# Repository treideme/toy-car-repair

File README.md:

# Mercedes Toy Repair

This repo contains schematics, drawings, and firmware of the controller
for my sons broken Mercedes.

See [my blogpost](https://reidemeister.com/blog/2022.07.04) for more information.

---- 
Pull requests are welcome. For major changes, please open an issue first to discuss what you would like to change.

## License
[MIT](LICENSE.md)

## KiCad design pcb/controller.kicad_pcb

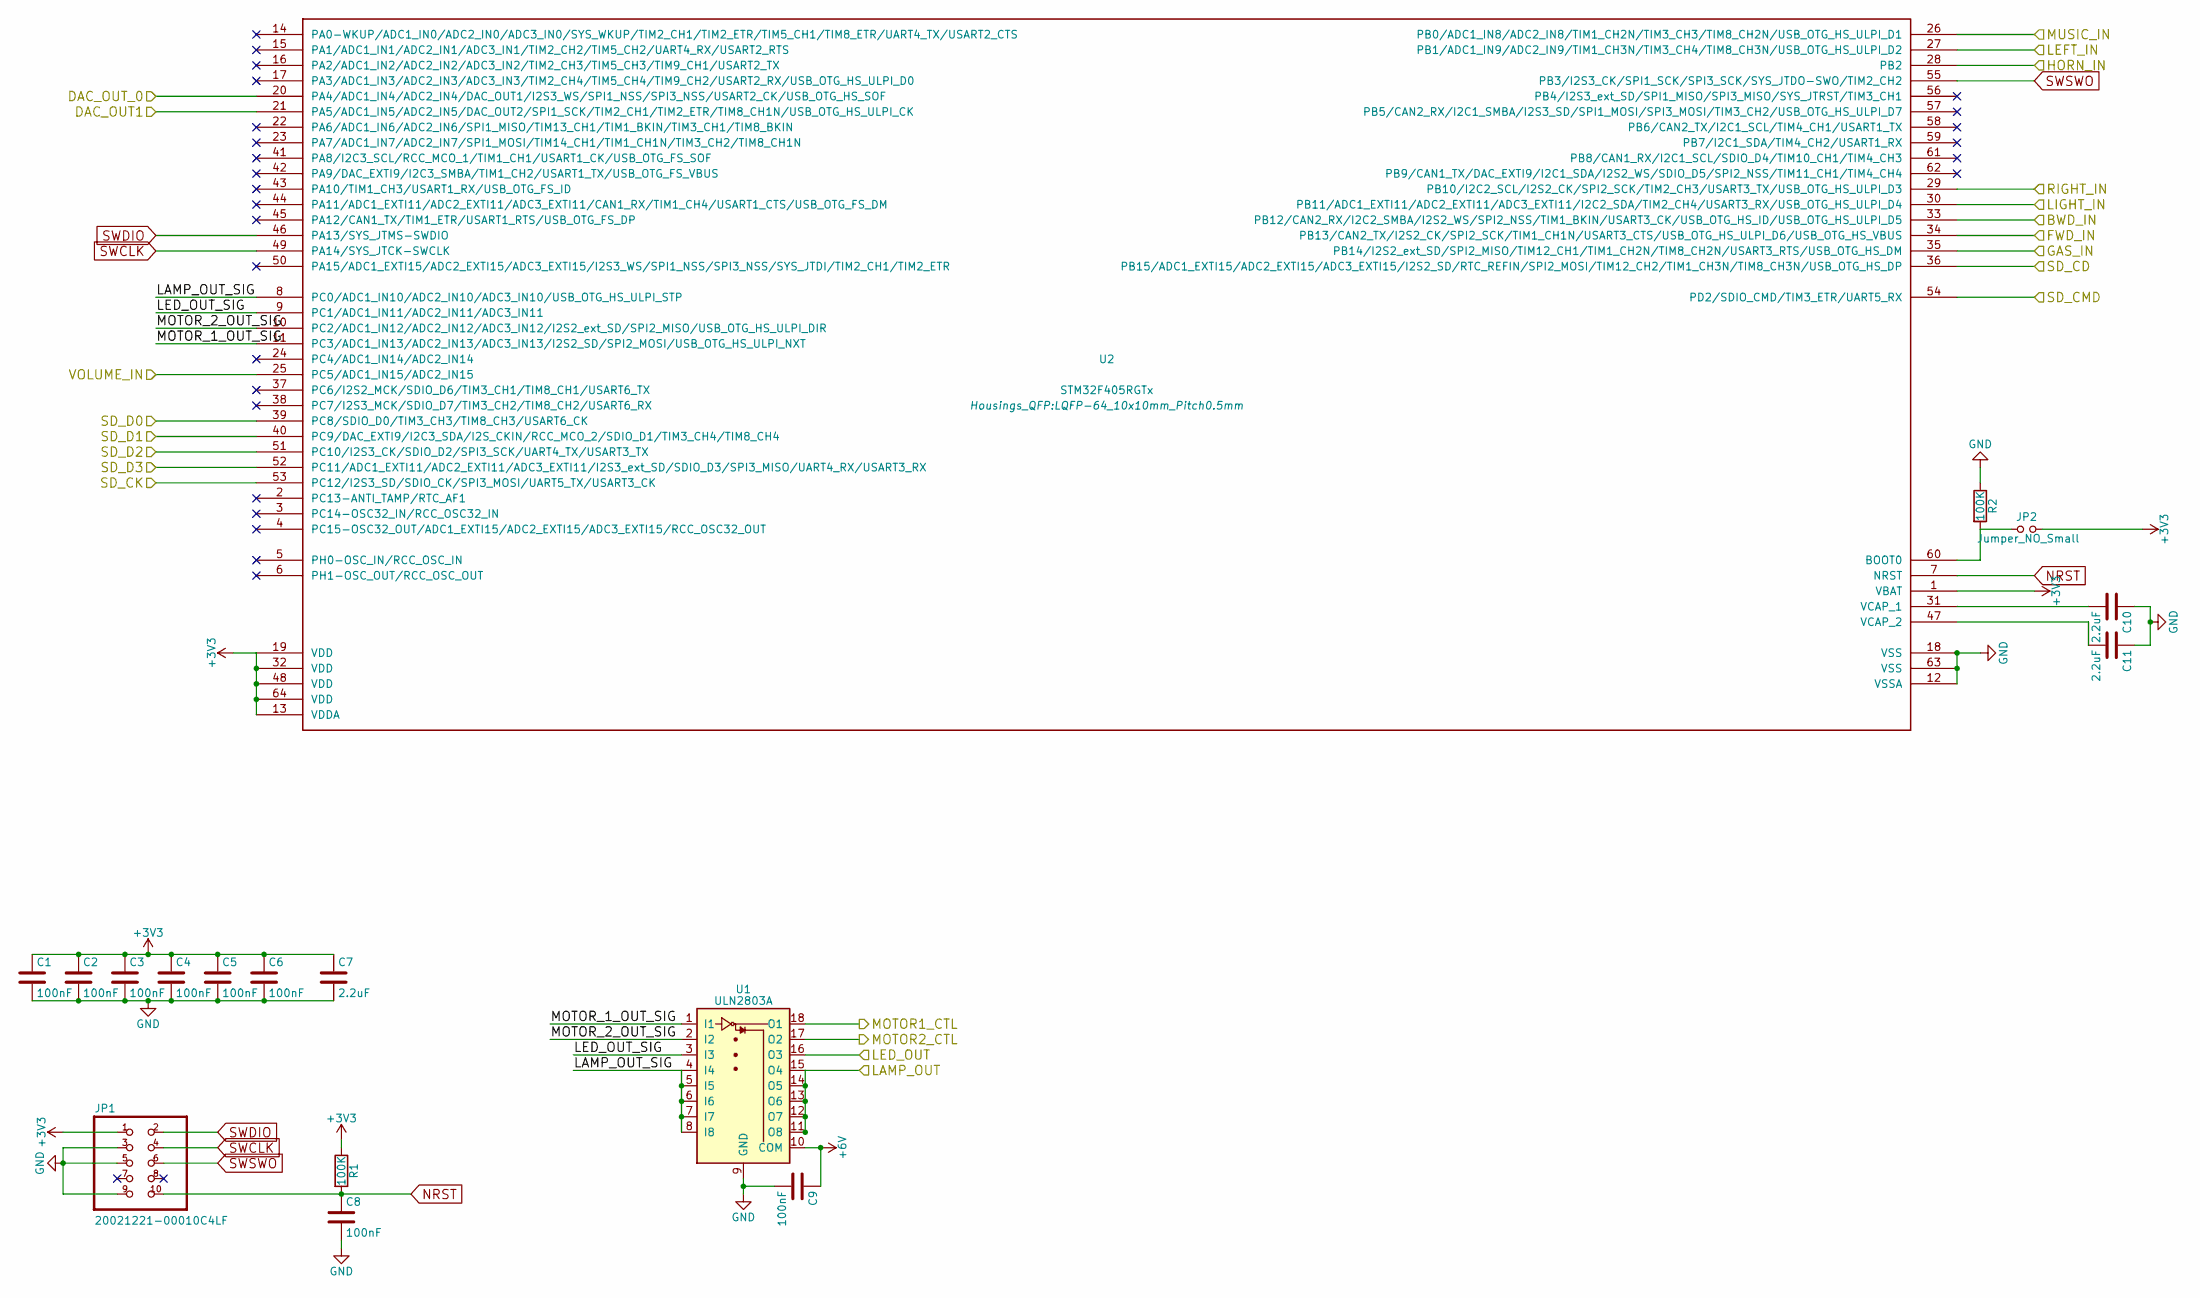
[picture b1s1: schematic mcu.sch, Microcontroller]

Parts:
C1, C2, C3, C4, C5, C6, C8, C9: 100nF; C_0603_HandSoldering; MFRPN GCM188R71C104KA37D; LCSC C184760
C7, C10, C11: 2.2uF; C_0603_HandSoldering; MFRPN GRM188B31A225KE33D; LCSC C85991
JP1: 20021221-00010C4LF
JP2: Jumper_NO_Small; SolderJumper-2_P1.3mm_Open_Pad1.0x1.5mm
R1, R2: 100K; R_0603_HandSoldering; MFRPN ERJUP3J104V; LCSC C491207
U1: ULN2803A; SOIC-18W_7.5x11.6mm_Pitch1.27mm; MFRPN ULN2803ADWR; LCSC C9683
U2: STM32F405RGTx; LQFP-64_10x10mm_Pitch0.5mm; MFRPN STM32F405RGT6; LCSC C15742

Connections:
+3V3: C1.1, C2.1, C3.1, C4.1, C5.1, C6.1, C7.1, JP1.1, JP2.2, R1.1, U2.1 (VBAT), U2.13 (VDDA), U2.19 (VDD), U2.32 (VDD), U2.48 (VDD), U2.64 (VDD); also elsewhere on the board
+6V: C9.1, U1.10 (COM); also elsewhere on the board
/External/BACKWARD_IN: U2.33 (PB12/CAN2_RX/I2C2_SMBA/I2S2_WS/SPI2_NSS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); also elsewhere on the board
/External/FORWARD_IN: U2.34 (PB13/CAN2_TX/I2S2_CK/SPI2_SCK/TIM1_CH1N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); also elsewhere on the board
/External/GAS_IN: U2.35 (PB14/I2S2_ext_SD/SPI2_MISO/TIM12_CH1/TI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); also elsewhere on the board
/External/HORN_IN: U2.28 (PB2); also elsewhere on the board
/External/LED_OUT: U1.16 (O3); also elsewhere on the board
/External/LEFT_IN: U2.27 (PB1/ADC1_IN9/ADC2_IN9/TIM1_CH3N/TIM3_CH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); also elsewhere on the board
/External/LIGHT_IN: U2.30 (PB11/ADC1_EXTI11/ADC2_EXTI11/ADC3_EXTI1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); also elsewhere on the board
/External/MUSIC_IN: U2.26 (PB0/ADC1_IN8/ADC2_IN8/TIM1_CH2N/TIM3_CH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); also elsewhere on the board
/External/RIGHT_IN: U2.29 (PB10/I2C2_SCL/I2S2_CK/SPI2_SCK/TIM2_CH3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); also elsewhere on the board
/External/SD_CMD: U2.54 (PD2/SDIO_CMD/TIM3_ETR/UART5_RX); also elsewhere on the board
/External/SD_D0: U2.39 (PC8/SDIO_D0/TIM3_CH3/TIM8_CH3/USART6_CK); also elsewhere on the board
/External/SD_D1: U2.40 (PC9/DAC_EXTI9/I2C3_SDA/I2S_CKIN/RCC_MCO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); also elsewhere on the board
/External/SD_D2: U2.51 (PC10/I2S3_CK/SDIO_D2/SPI3_SCK/UART4_TX/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); also elsewhere on the board
/External/SD_D3: U2.52 (PC11/ADC1_EXTI11/ADC2_EXTI11/ADC3_EXTI1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); also elsewhere on the board
/External/VOLUME_IN: U2.25 (PC5/ADC1_IN15/ADC2_IN15); also elsewhere on the board
/Microcontroller/DAC_OUT1: U2.21 (PA5/ADC1_IN5/ADC2_IN5/DAC_OUT2/SPI1_SCK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); also elsewhere on the board
/Microcontroller/DAC_OUT_0: U2.20 (PA4/ADC1_IN4/ADC2_IN4/DAC_OUT1/I2S3_WS/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); also elsewhere on the board
/Microcontroller/LAMP_OUT: U1.11 (O8), U1.12 (O7), U1.13 (O6), U1.14 (O5), U1.15 (O4); also elsewhere on the board
/Microcontroller/LAMP_OUT_SIG: U1.4 (I4), U1.5 (I5), U1.6 (I6), U1.7 (I7), U1.8 (I8), U2.8 (PC0/ADC1_IN10/ADC2_IN10/ADC3_IN10/USB_O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)
/Microcontroller/LED_OUT_SIG: U1.3 (I3), U2.9 (PC1/ADC1_IN11/ADC2_IN11/ADC3_IN11)
/Microcontroller/MOTOR1_CTL: U1.18 (O1); also elsewhere on the board
/Microcontroller/MOTOR2_CTL: U1.17 (O2); also elsewhere on the board
/Microcontroller/MOTOR_1_OUT_SIG: U1.1 (I1), U2.11 (PC3/ADC1_IN13/ADC2_IN13/ADC3_IN13/I2S2_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)
/Microcontroller/MOTOR_2_OUT_SIG: U1.2 (I2), U2.10 (PC2/ADC1_IN12/ADC2_IN12/ADC3_IN12/I2S2_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)
/Microcontroller/SD_CD: U2.36 (PB15/ADC1_EXTI15/ADC2_EXTI15/ADC3_EXTI1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); also elsewhere on the board
/Microcontroller/SD_CK: U2.53 (PC12/I2S3_SD/SDIO_CK/SPI3_MOSI/UART5_TX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); also elsewhere on the board
GND: C1.2, C2.2, C3.2, C4.2, C5.2, C6.2, C7.2, C8.2, C9.2, C10.1, C11.1, JP1.3, JP1.5, JP1.9, R2.1, U1.9 (GND), U2.12 (VSSA), U2.18 (VSS), U2.63 (VSS); also elsewhere on the board
NRST: C8.1, JP1.10, R1.2, U2.7 (NRST)
unnamed: C10.2, U2.31 (VCAP_1)
unnamed: C11.2, U2.47 (VCAP_2)
unnamed: JP2.1, R2.2, U2.60 (BOOT0)
SWCLK: JP1.4, U2.49 (PA14/SYS_JTCK-SWCLK)
SWDIO: JP1.2, U2.46 (PA13/SYS_JTMS-SWDIO)
SWSWO: JP1.6, U2.55 (PB3/I2S3_CK/SPI1_SCK/SPI3_SCK/SYS_JTDO-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)

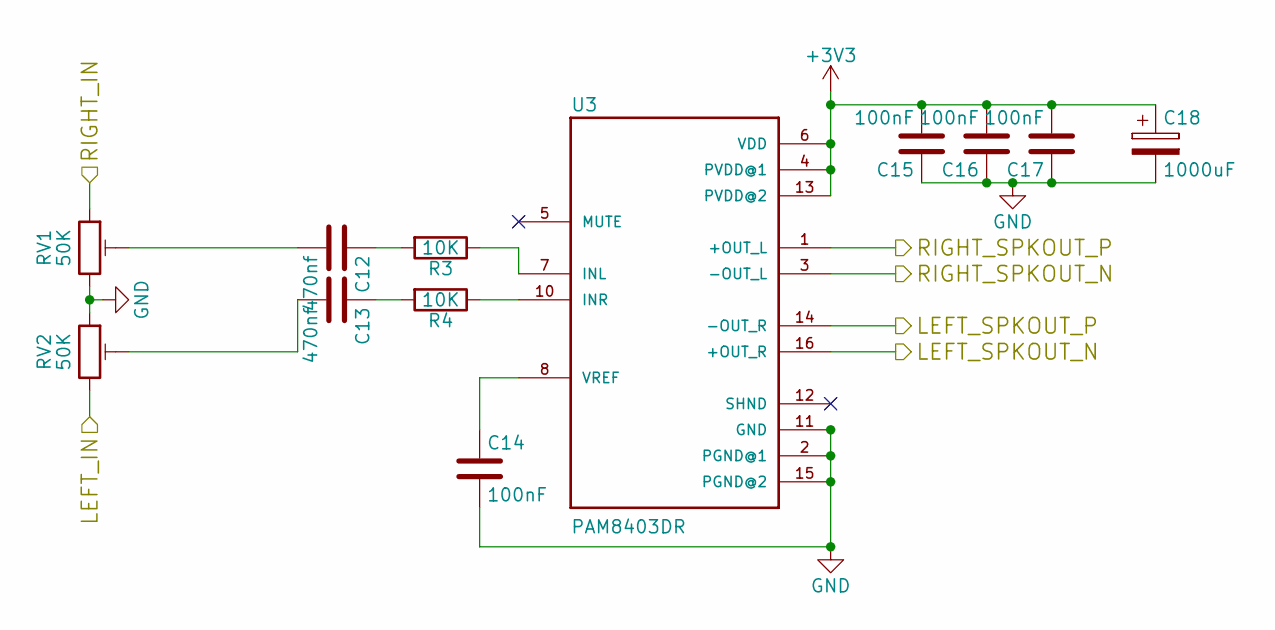
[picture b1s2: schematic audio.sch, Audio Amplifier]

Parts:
C12, C13: 470nf; C_0603_HandSoldering; MFRPN CC0603JRX7R6BB474; LCSC C519557
C14, C15, C16, C17: 100nF; C_0603_HandSoldering; MFRPN GCM188R71C104KA37D; LCSC C184760
C18: 1000uF; CP_Elec_10x10; MFRPN EEEFC1A102AP; LCSC C401617
R3, R4: 10K; R_0603_HandSoldering; MFRPN ERJ3RBD1002V; LCSC C191318
RV1, RV2: 50K; TRIM_3314J-1-202E; MFRPN 3314J-1-503E; LCSC C50895
U3: PAM8403DR; SOIC127P605X150-16N; MFRPN PAM8403D; LCSC C348830

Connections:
+3V3: C15.2, C16.2, C17.2, C18.1, U3.4 (PVDD@1), U3.6 (VDD), U3.13 (PVDD@2); also elsewhere on the board
/Audio/LEFT_SPKOUT_N: U3.16 (+OUT_R); also elsewhere on the board
/Audio/LEFT_SPKOUT_P: U3.14 (-OUT_R); also elsewhere on the board
/Audio/RIGHT_SPKOUT_N: U3.3 (-OUT_L); also elsewhere on the board
/Audio/RIGHT_SPKOUT_P: U3.1 (+OUT_L); also elsewhere on the board
/Microcontroller/DAC_OUT1: RV2.3; also elsewhere on the board
/Microcontroller/DAC_OUT_0: RV1.1; also elsewhere on the board
GND: C14.2, C15.1, C16.1, C17.1, C18.2, RV1.3, RV2.1, U3.2 (PGND@1), U3.11 (GND), U3.15 (PGND@2); also elsewhere on the board
unnamed: C12.1, R3.2
unnamed: C12.2, RV1.2
unnamed: C13.1, R4.2
unnamed: C13.2, RV2.2
unnamed: C14.1, U3.8 (VREF)
unnamed: R3.1, U3.7 (INL)
unnamed: R4.1, U3.10 (INR)

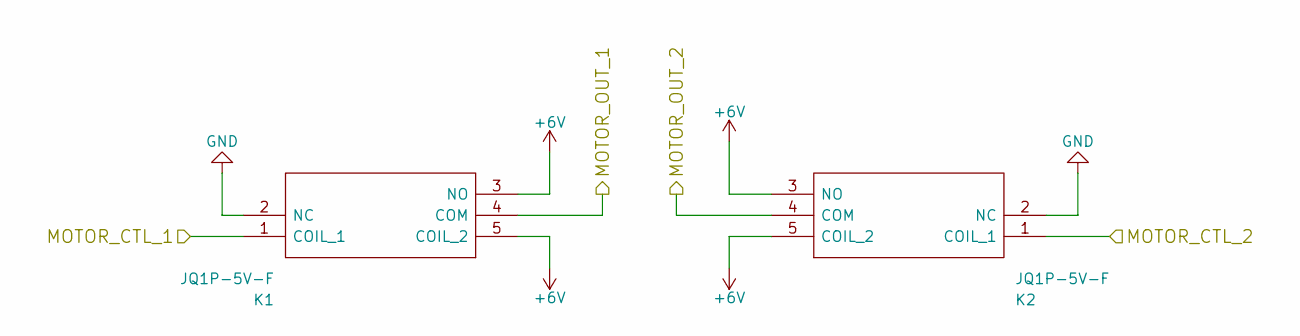
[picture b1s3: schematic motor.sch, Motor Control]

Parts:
K1, K2: JQ1P-5V-F; JQ1P5VF; Manufacturer_Part_Number JQ1P-5V-F; Mouser Part Number 769-JQ1P-5V-F

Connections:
+6V: K1.3 (NO), K1.5 (COIL_2), K2.3 (NO), K2.5 (COIL_2); also elsewhere on the board
/External/MOTOR_OUT_1: K1.4 (COM); also elsewhere on the board
/External/MOTOR_OUT_2: K2.4 (COM); also elsewhere on the board
/Microcontroller/MOTOR1_CTL: K1.1 (COIL_1); also elsewhere on the board
/Microcontroller/MOTOR2_CTL: K2.1 (COIL_1); also elsewhere on the board
GND: K1.2 (NC), K2.2 (NC); also elsewhere on the board

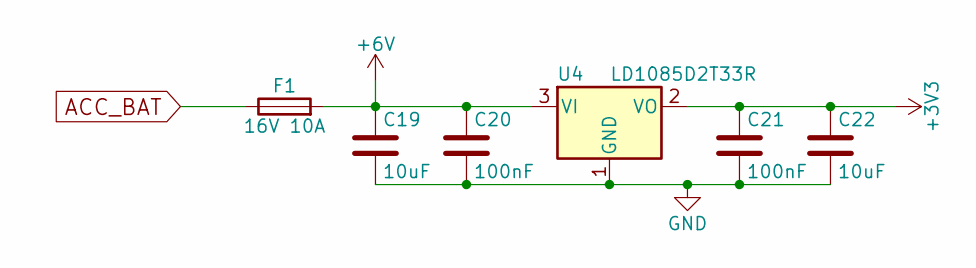
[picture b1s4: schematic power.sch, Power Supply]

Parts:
C19, C22: 10uF; C_0805_HandSoldering; MFRPN GRM21BR61C106KE15L; LCSC C77075
C20, C21: 100nF; C_0603_HandSoldering; MFRPN GCM188R71C104KA37D; LCSC C184760
F1: 16V 10A; Fuse_SMD2920; MFRPN 2920L500/16MR; LCSC C207091
U4: LD1085D2T33R; TO-263-2; MFRPN LD1085D2T33R; LCSC C7913

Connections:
+3V3: C21.1, C22.1, U4.2 (VO); also elsewhere on the board
+6V: C19.1, C20.1, F1.2, U4.3 (VI); also elsewhere on the board
ACC_BAT: F1.1; also elsewhere on the board
GND: C19.2, C20.2, C21.2, C22.2, U4.1 (GND); also elsewhere on the board

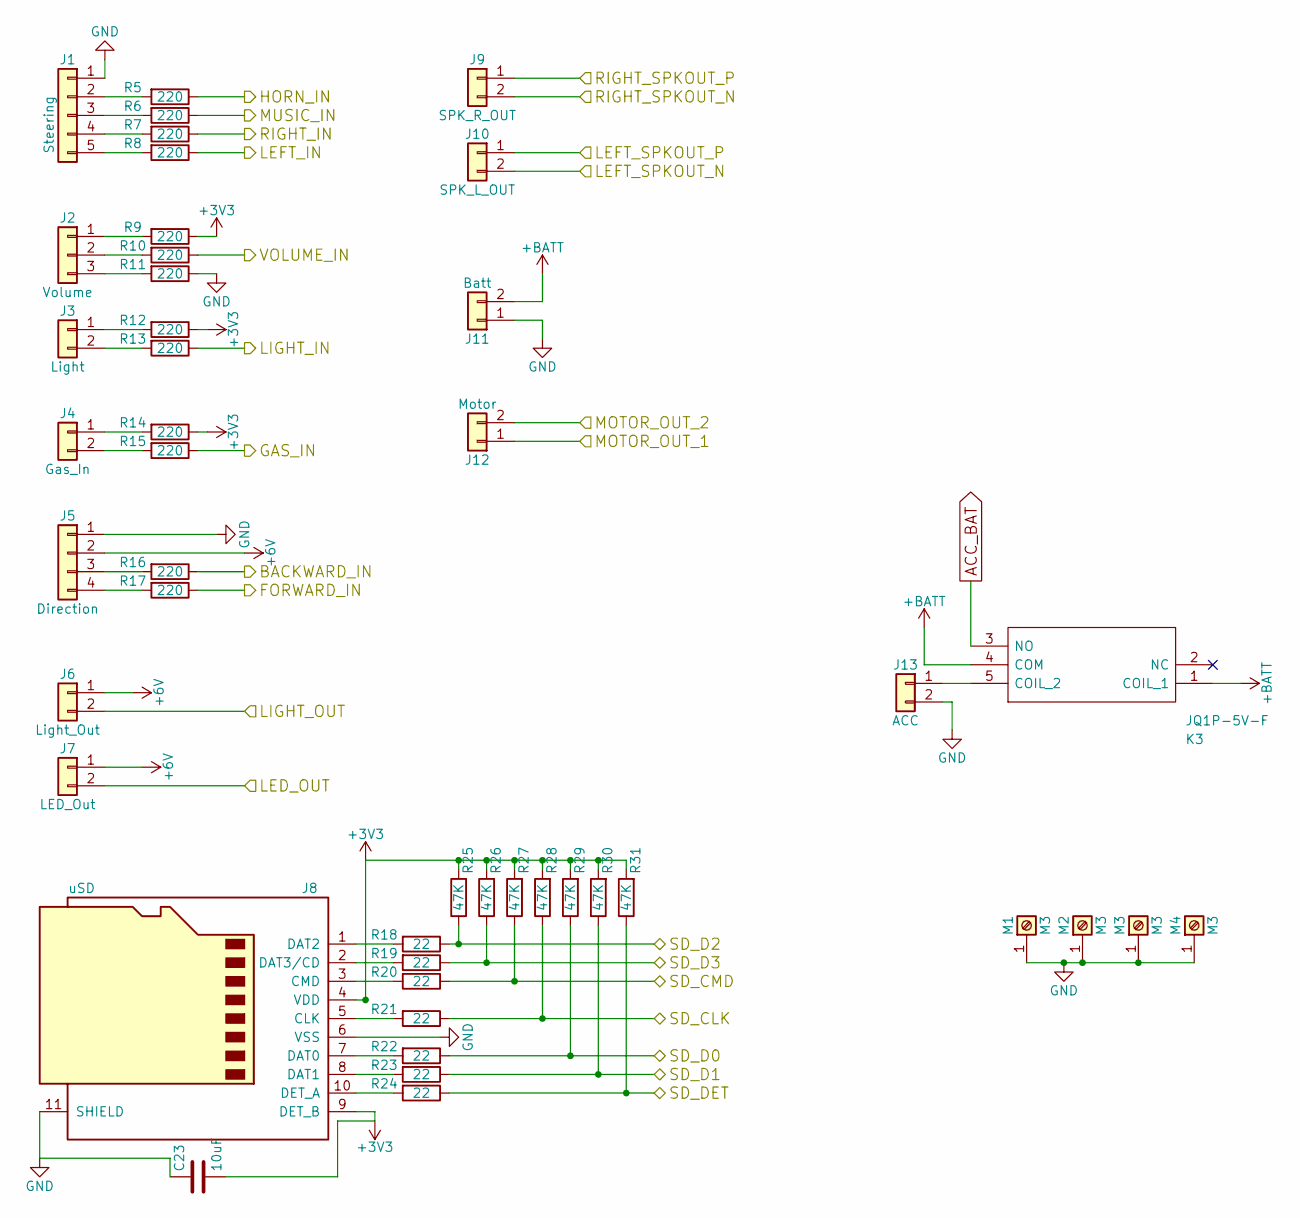
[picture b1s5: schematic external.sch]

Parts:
C23: 10uF; C_0805_HandSoldering; MFRPN GRM21BR61C106KE15L; LCSC C77075
J1: Steering; JST_XH_B05B-XH-A_05x2.50mm_Straight; MFRPN B5B-XH-A(LF)(SN); LCSC C157991
J2: Volume; JST_XH_B03B-XH-A_03x2.50mm_Straight; LCSC C144394
J3: Light; JST_XH_B02B-XH-A_02x2.50mm_Straight; MFRPN B2B-XH-A(LF)(SN); LCSC C158012
J4: Gas_In; JST_XH_B02B-XH-A_02x2.50mm_Straight; MFRPN B2B-XH-A(LF)(SN); LCSC C158012
J5: Direction; JST_XH_B04B-XH-A_04x2.50mm_Straight; MFRPN B4B-XH-A(LF)(SN); LCSC C144395
J6: Light_Out; JST_XH_B02B-XH-A_02x2.50mm_Straight; MFRPN B2B-XH-A(LF)(SN); LCSC C158012
J7: LED_Out; JST_XH_B02B-XH-A_02x2.50mm_Straight; MFRPN B2B-XH-A(LF)(SN); LCSC C158012
J8: uSD; Hirose_DM3AT-SF-PEJM5; MFRPN DM3AT-SF-PEJM5; LCSC C114218
J9: SPK_R_OUT; JST_XH_B02B-XH-A_02x2.50mm_Straight; MFRPN B2B-XH-A(LF)(SN); LCSC C158012
J10: SPK_L_OUT; JST_XH_B02B-XH-A_02x2.50mm_Straight; MFRPN B2B-XH-A(LF)(SN); LCSC C158012
J11: Batt; JST_VH_B2P-VH-B_2x3.96mm_Vertical; MFRPN B2P-VH(LF)(SN); LCSC C160315
J12: Motor; JST_VH_B2P-VH-B_2x3.96mm_Vertical; MFRPN B2P-VH(LF)(SN); LCSC C160315
J13: ACC; JST_XH_B02B-XH-A_02x2.50mm_Straight; MFRPN B2B-XH-A(LF)(SN); LCSC C158012
K3: JQ1P-5V-F; JQ1P5VF; Manufacturer_Part_Number JQ1P-5V-F; Mouser Part Number 769-JQ1P-5V-F
M1, M2, M3, M4: M3; MountingHole_3.2mm_M3_Pad
R5, R6, R7, R8, R9, R10, R11, R12, R13, R14, R15, R16, R17: 220; R_0603_HandSoldering; MFRPN ERJ3GEYJ221V; LCSC C403454
R18, R19, R20, R21, R22, R23, R24: 22; R_0603_HandSoldering; MFRPN ERJ3GEYJ220V; LCSC C278638
R25, R26, R27, R28, R29, R30, R31: 47K; R_0603_HandSoldering; MFRPN ERJ3GEYJ473V; LCSC C278642

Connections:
+3V3: C23.2, J8.4 (VDD), J8.9 (DET_B), R9.1, R12.1, R14.1, R25.2, R26.2, R27.2, R28.2, R29.2, R30.2, R31.2; also elsewhere on the board
+6V: J5.2, J6.1, J7.1; also elsewhere on the board
+BATT: J11.2, K3.1 (COIL_1), K3.4 (COM)
/Audio/LEFT_SPKOUT_N: J10.2; also elsewhere on the board
/Audio/LEFT_SPKOUT_P: J10.1; also elsewhere on the board
/Audio/RIGHT_SPKOUT_N: J9.2; also elsewhere on the board
/Audio/RIGHT_SPKOUT_P: J9.1; also elsewhere on the board
/External/BACKWARD_IN: R16.1; also elsewhere on the board
/External/FORWARD_IN: R17.1; also elsewhere on the board
/External/GAS_IN: R15.1; also elsewhere on the board
/External/HORN_IN: R5.1; also elsewhere on the board
/External/LED_OUT: J7.2; also elsewhere on the board
/External/LEFT_IN: R8.1; also elsewhere on the board
/External/LIGHT_IN: R13.1; also elsewhere on the board
/External/MOTOR_OUT_1: J12.1; also elsewhere on the board
/External/MOTOR_OUT_2: J12.2; also elsewhere on the board
/External/MUSIC_IN: R6.1; also elsewhere on the board
/External/RIGHT_IN: R7.1; also elsewhere on the board
/External/SD_CMD: R20.1, R27.1; also elsewhere on the board
/External/SD_D0: R22.1, R29.1; also elsewhere on the board
/External/SD_D1: R23.1, R30.1; also elsewhere on the board
/External/SD_D2: R18.1, R25.1; also elsewhere on the board
/External/SD_D3: R19.1, R26.1; also elsewhere on the board
/External/VOLUME_IN: R10.1; also elsewhere on the board
/Microcontroller/LAMP_OUT: J6.2; also elsewhere on the board
/Microcontroller/SD_CD: R24.1, R31.1; also elsewhere on the board
/Microcontroller/SD_CK: R21.1, R28.1; also elsewhere on the board
ACC_BAT: K3.3 (NO); also elsewhere on the board
GND: C23.1, J1.1, J5.1, J8.6 (VSS), J8.11 (SHIELD), J11.1, J13.2, M1.1, M2.1, M3.1, M4.1, R11.1; also elsewhere on the board
unnamed: J1.2, R5.2
unnamed: J1.3, R6.2
unnamed: J1.4, R7.2
unnamed: J1.5, R8.2
unnamed: J2.1, R9.2
unnamed: J2.2, R10.2
unnamed: J2.3, R11.2
unnamed: J3.1, R12.2
unnamed: J3.2, R13.2
unnamed: J4.1, R14.2
unnamed: J4.2, R15.2
unnamed: J5.3, R16.2
unnamed: J5.4, R17.2
unnamed: J8.1 (DAT2), R18.2
unnamed: J8.2 (DAT3/CD), R19.2
unnamed: J8.3 (CMD), R20.2
unnamed: J8.5 (CLK), R21.2
unnamed: J8.7 (DAT0), R22.2
unnamed: J8.8 (DAT1), R23.2
unnamed: J8.10 (DET_A), R24.2
unnamed: J13.1, K3.5 (COIL_2)

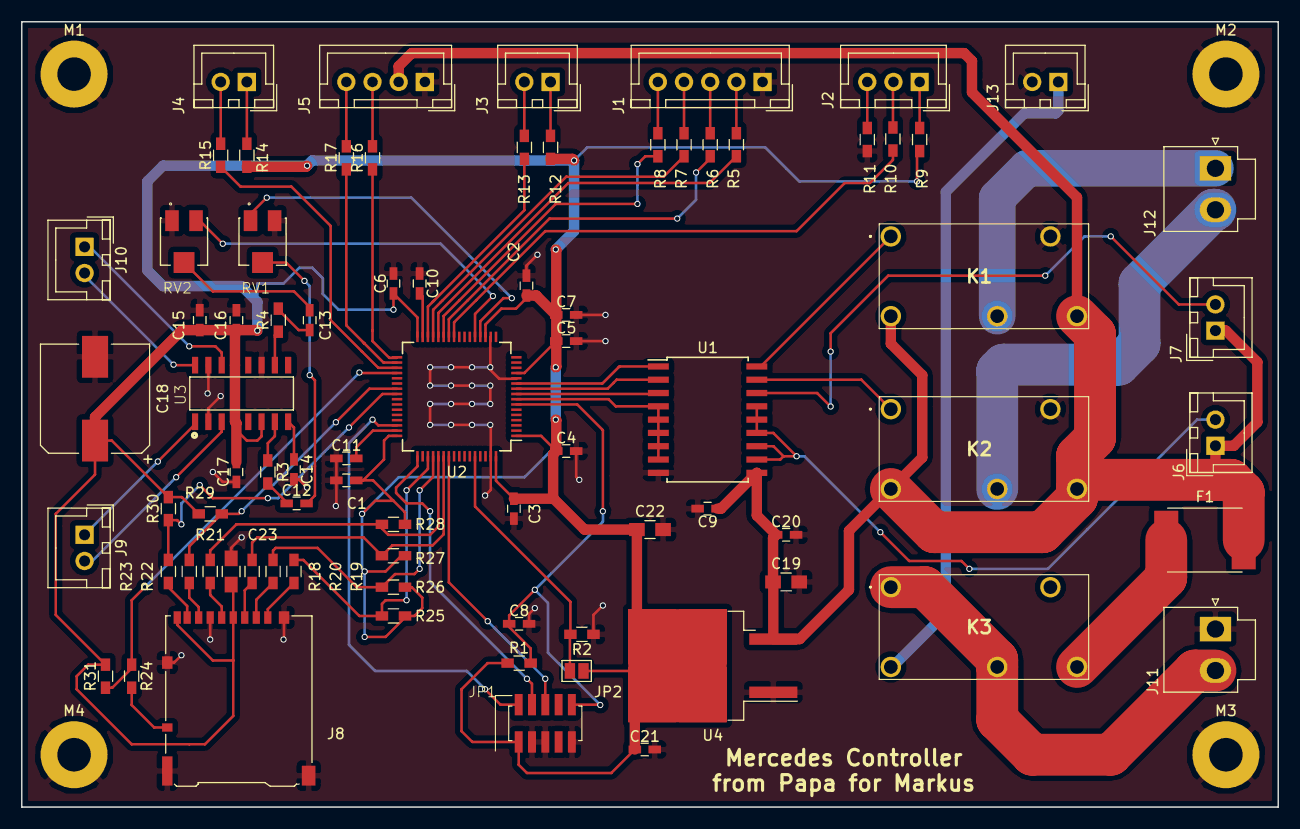
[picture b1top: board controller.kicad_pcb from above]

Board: 2 copper layers, 120.0 x 75.0 mm, 83 parts (0 on the bottom side), 72 nets.

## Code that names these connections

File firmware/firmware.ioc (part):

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PB13.GPIOParameters=GPIO_PuPd,GPIO_Label
Mcu.UserName=STM32F405RGTx
PB10.GPIO_PuPd=GPIO_PULLUP
PC12.Signal=SDIO_CK
PC10.Signal=SDIO_D2
PB14.GPIO_Label=GAS_BTN
PC0.GPIOParameters=GPIO_PuPd,GPIO_Label
PC0.GPIO_Label=LAMP_OUT
PB0.GPIO_Label=MUSIC_BTN
PD2.GPIOParameters=GPIO_PuPd
PB11.GPIO_PuPd=GPIO_PULLDOWN
PB13.GPIO_Label=FWD_BTN
PB11.Signal=GPIO_Input
PB13.Signal=GPIO_Input
PB15.Signal=GPIO_Input
RCC.SYSCLKSource=RCC_SYSCLKSOURCE_PLLCLK
PC1.GPIOParameters=GPIO_PuPd,GPIO_Label
PB1.GPIO_PuPd=GPIO_PULLUP
PC3.Signal=GPIO_Output
RCC.HSE_VALUE=8000000
PB2.Signal=GPIO_Input
PC1.GPIO_PuPd=GPIO_PULLDOWN
PB12.GPIO_Label=BWD_BTN
PB0.GPIOParameters=GPIO_PuPd,GPIO_Label
PA14.Mode=Serial_Wire
PB1.GPIO_Label=LEFT_BTN
PC9.Mode=SD_4_bits_Wide_bus
PB2.GPIO_PuPd=GPIO_PULLUP
PC8.GPIOParameters=GPIO_PuPd
Mcu.Package=LQFP64
PB14.GPIO_PuPd=GPIO_PULLDOWN
PB1.Signal=GPIO_Input
PB15.GPIO_PuPd=GPIO_PULLUP
PC11.Mode=SD_4_bits_Wide_bus
PB14.GPIOParameters=GPIO_PuPd,GPIO_Label
PC5.Signal=ADCx_IN15
PB10.GPIOParameters=GPIO_PuPd,GPIO_Label
PC0.GPIO_PuPd=GPIO_PULLDOWN
PC2.GPIO_Label=MOTOR_2
PD2.GPIO_PuPd=GPIO_PULLUP
PC11.Signal=SDIO_D3
PC8.Signal=SDIO_D0
PC2.Signal=GPIO_Output
PC10.Mode=SD_4_bits_Wide_bus
PB11.GPIO_Label=LIGHT_BTN
PC0.Signal=GPIO_Output
PC3.GPIOParameters=GPIO_PuPd,GPIO_Label
PA13.Signal=SYS_JTMS-SWDIO
PB10.GPIO_Label=RIGHT_BTN
PC5.GPIOParameters=GPIO_Label
PB2.GPIOParameters=GPIO_PuPd,GPIO_Label
PB11.GPIOParameters=GPIO_PuPd,GPIO_Label
PB10.Signal=GPIO_Input
PB14.Signal=GPIO_Input
PD2.Mode=SD_4_bits_Wide_bus
PA5.Signal=COMP_DAC2_group
PC12.Mode=SD_4_bits_Wide_bus
board=custom
PB13.GPIO_PuPd=GPIO_PULLDOWN
PB15.GPIO_Label=SDIO_CD
PC2.GPIOParameters=GPIO_PuPd,GPIO_Label
PC1.GPIO_Label=LED_OUT
PC2.GPIO_PuPd=GPIO_PULLDOWN
PB15.GPIOParameters=GPIO_PuPd,GPIO_Label
PA13.Mode=Serial_Wire
Mcu.Name=STM32F405RGTx
PC8.Mode=SD_4_bits_Wide_bus
PC8.GPIO_PuPd=GPIO_PULLUP
PA4.Signal=COMP_DAC1_group
RCC.SYSCLKFreq_VALUE=168000000
PC5.GPIO_Label=VOLUMNE_IN
PA14.Signal=SYS_JTCK-SWCLK
PB2.GPIO_Label=HORN_BTN
PC3.GPIO_Label=MOTOR_1
PC9.Signal=SDIO_D1
PD2.Signal=SDIO_CMD
PB12.GPIO_PuPd=GPIO_PULLDOWN
PB0.Signal=GPIO_Input
PC1.Signal=GPIO_Output
PB12.GPIOParameters=GPIO_PuPd,GPIO_Label
PB12.Signal=GPIO_Input
PB0.GPIO_PuPd=GPIO_PULLUP
PC3.GPIO_PuPd=GPIO_PULLDOWN
PB1.GPIOParameters=GPIO_PuPd,GPIO_Label

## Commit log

2020-08-01 Initial Generated Firmware
2020-08-01 First Main
2020-08-01 Resolved #5
2020-08-02 Proof of concept Fat reading
2020-08-18 First schematic draft
2020-08-20 First submitted PCB
2020-10-22 Fixes after board arrived
2020-10-26 Motor controls working
2020-10-26 SD Fixes
2020-10-26 Timer not working
2020-10-26 WAV playback working
2020-10-27 Playlist working
2022-07-04 Prototype (#1)
    * Initial Generated Firmware
    * First Main
    * Resolved #5
    * Proof of concept Fat reading
    * First schematic draft
    * First submitted PCB
2022-07-04 Added Blog link
2025-10-19 Updated blog link
